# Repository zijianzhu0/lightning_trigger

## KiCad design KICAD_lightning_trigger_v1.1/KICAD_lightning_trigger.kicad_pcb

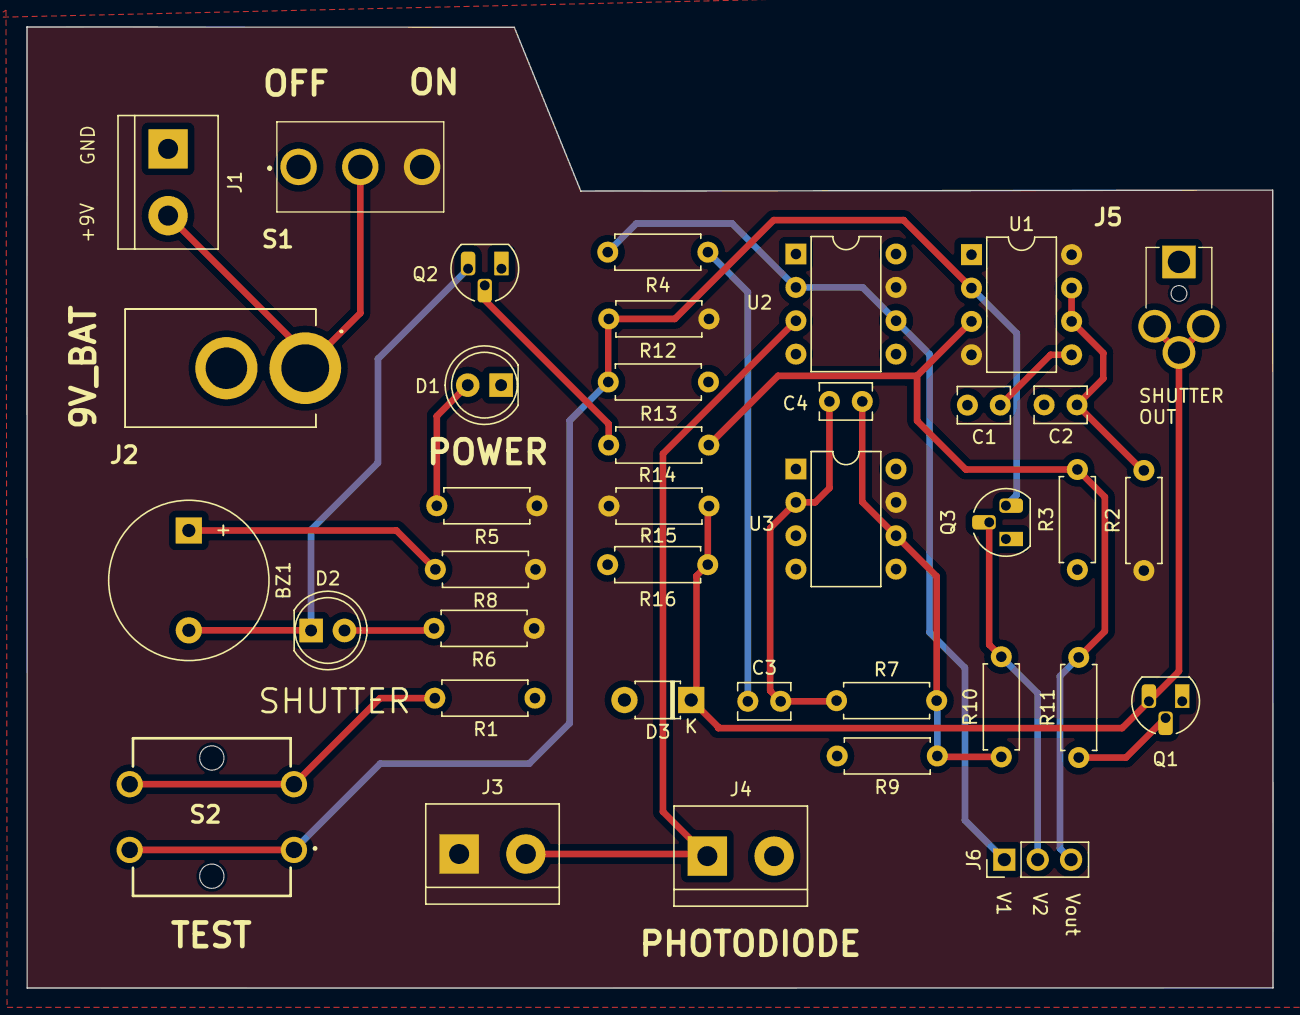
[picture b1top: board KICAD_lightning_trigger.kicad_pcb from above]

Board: 2 copper layers, 94.8 x 73.1 mm, 38 parts (0 on the bottom side), 21 nets.

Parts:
BZ1: Buzzer; Buzzer_12x9.5RM7.6
C1, C2: 0.01u; C_Disc_D3.8mm_W2.6mm_P2.50mm
C3: 47n; C_Disc_D3.8mm_W2.6mm_P2.50mm
C4: 4.7n; C_Disc_D3.8mm_W2.6mm_P2.50mm
D1, D2: LED; LED_D5.0mm_Clear
D3: D_Zener; D_T-1_P5.08mm_Horizontal
J1, J3, J4: Screw_Terminal_01x02; TerminalBlock_TE-2_P5.08mm
J2: Barrel_Jack; BerralJack_PJ037A
J5: SJ1-2503A; AudioJack_SJ12503A
J6: Conn_01x03_Pin; PinHeader_1x03_P2.54mm_Vertical
Q1, Q2, Q3: 2N3904; TO-92_HandSolder
R1, R4, R12, R16: 1k; R_Axial_DIN0207_L6.3mm_D2.5mm_P7.62mm_Horizontal
R2: 220k; R_Axial_DIN0207_L6.3mm_D2.5mm_P7.62mm_Horizontal
R3, R7, R11, R14: 10k; R_Axial_DIN0207_L6.3mm_D2.5mm_P7.62mm_Horizontal
R5, R6: 500; R_Axial_DIN0207_L6.3mm_D2.5mm_P7.62mm_Horizontal
R8, R9, R10: 100; R_Axial_DIN0207_L6.3mm_D2.5mm_P7.62mm_Horizontal
R13: 5.1k; R_Axial_DIN0207_L6.3mm_D2.5mm_P7.62mm_Horizontal
R15: 2k; R_Axial_DIN0207_L6.3mm_D2.5mm_P7.62mm_Horizontal
S1: 100SP1T1B1M2QEH; ToggleSwitch_100SP1T1B4M2QE
S2: B3F-4055
U1: NE555P; DIP-8_W7.62mm
U2, U3: LM741; DIP-8_W7.62mm

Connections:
+9V: J1.2, J2.1, S1.2 (COM)
/SHUTTER: D3.1 (K), J5.2 (TIP_1), J5.3 (TIP_2), J5.4 (RING), Q1.3 (C), R15.1, R16.2
/SHUTTER_ON: BZ1.2 (+), D2.1 (K), Q2.3 (C)
/TRIG: Q3.3 (C), R12.1, R13.2, S2.1, S2.2, U1.2 (TR)
/V1: J6.1, R4.1, U2.2 (-), U2.6
/V2: J6.2, Q3.2 (B), R10.2
/VCC: J3.1, R2.1, R5.1, R6.1, R8.1, R12.2, R15.2, S1.3 (NO), U1.4 (R), U1.8 (VCC), U2.7 (V+), U3.7 (V+)
/Vin: J3.2, J4.1, U2.3 (+)
/Vout: J6.3, R3.2, R11.2, R14.2, U1.3 (Q)
GND: C1.1, C2.1, D1.1 (K), D3.2 (A), J1.1, J2.2, J4.2, J5.1 (SLEEVE), Q1.1 (E), Q2.1 (E), Q3.1 (E), R1.2, R3.1, R9.2, R13.1, R16.1, U1.1 (GND), U2.4 (V-), U3.3 (+), U3.4 (V-)
unnamed: BZ1.1 (-), R8.2
unnamed: C3.1, R4.2
unnamed: C4.2, R7.2, R9.1, R10.1, U3.6
unnamed: D1.2 (A), R5.2
unnamed: D2.2 (A), R6.2
unnamed: Q1.2 (B), R11.1
unnamed: Q2.2 (B), R14.1
unnamed: R1.1, S2.3, S2.4
unnamed: C1.2, U1.5 (CV)
unnamed: C2.2, R2.2, U1.6 (THR), U1.7 (DIS)
unnamed: C3.2, C4.1, R7.1, U3.2 (-)

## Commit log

2025-06-20 added files
2025-06-20 added validation submodule
